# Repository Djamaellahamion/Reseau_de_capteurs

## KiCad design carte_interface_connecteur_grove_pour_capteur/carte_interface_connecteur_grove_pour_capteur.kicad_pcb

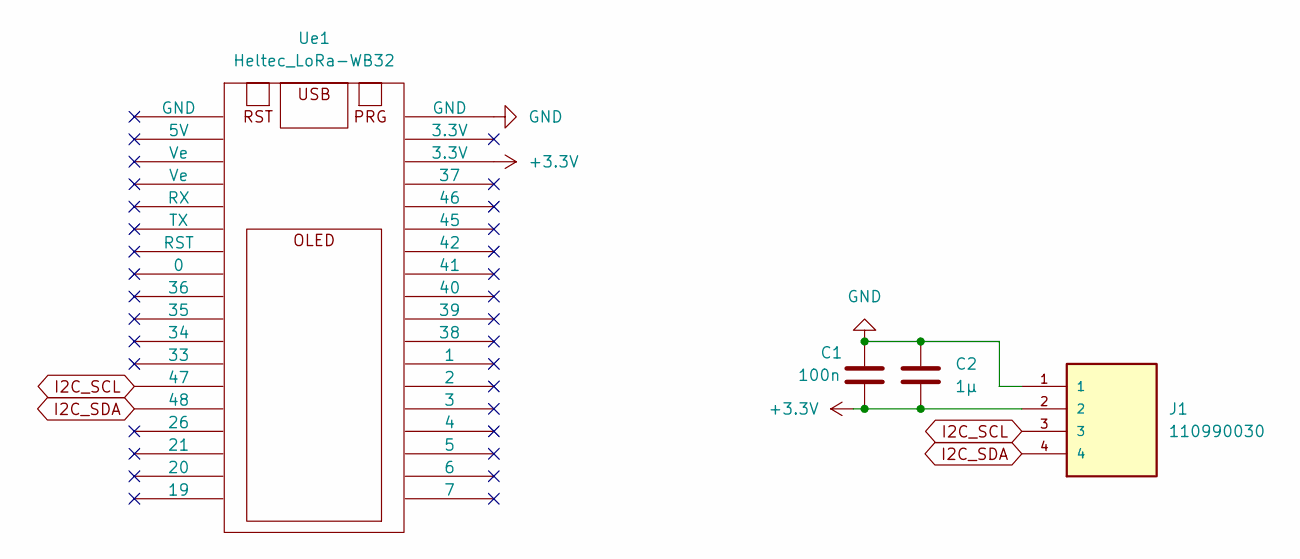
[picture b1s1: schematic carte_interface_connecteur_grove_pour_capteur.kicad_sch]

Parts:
C1: 100n; C_0805
C2: 1µ; C_0805
J1: 110990030; Grove_female_header; PARTREV A
Ue1: Heltec_LoRa-WB32; Heltec_WiFi_LoRa_V2_pin_size_2mm

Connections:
+3.3V: C1.2, C2.2, J1.2, Ue1.34 (3.3V)
GND: C1.1, C2.1, J1.1, Ue1.36 (GND)
I2C_SCL: J1.3, Ue1.13 (47)
I2C_SDA: J1.4, Ue1.14 (48)

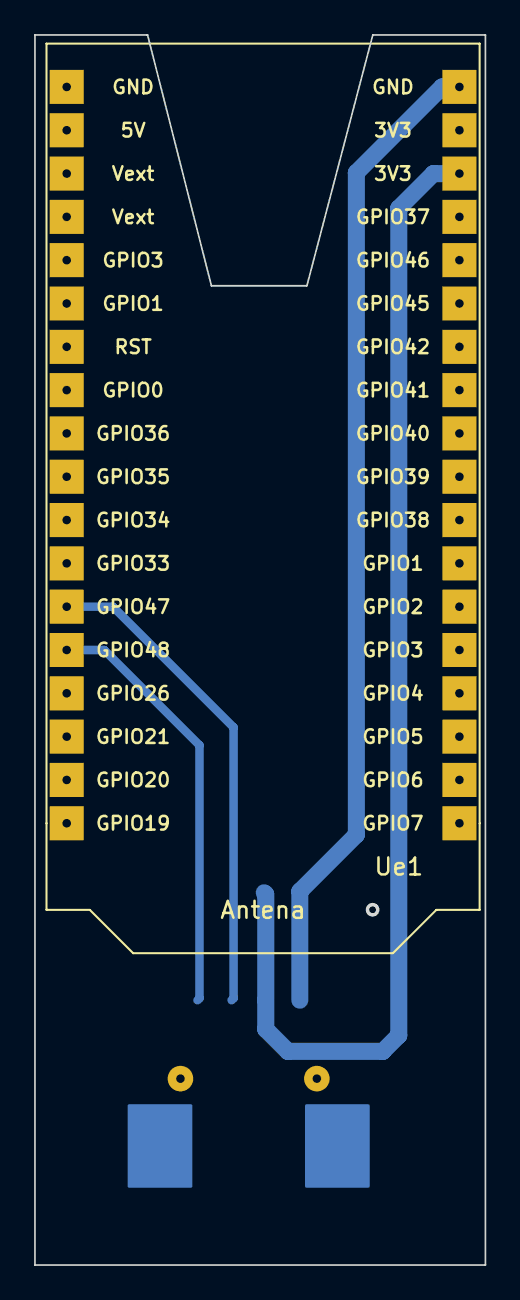
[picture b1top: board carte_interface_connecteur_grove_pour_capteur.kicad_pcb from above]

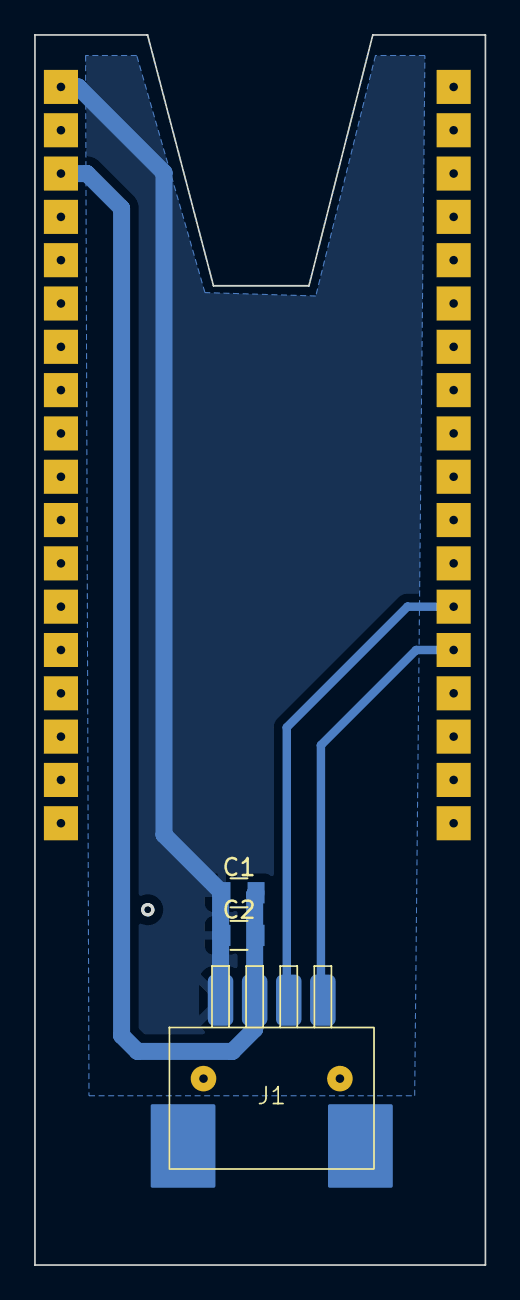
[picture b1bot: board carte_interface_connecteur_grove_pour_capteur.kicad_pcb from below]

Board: 2 copper layers, 26.4 x 72.1 mm, 4 parts (3 on the bottom side), 4 nets.

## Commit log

2023-05-17 Rename LoRaSender_basic.ino to LoRaSender_basic_TTGO.ino
2023-05-17 Rename Wireless Access Raspberry.txt to quelques liens utiles pour Raspberry
2023-05-17 Update quelques liens utiles pour Raspberry
2023-05-23 Create Serveur raspberry Salle blanche
2023-06-03 Update and rename quelques liens utiles pour Raspberry to quelques liens utiles pour Raspberryque
2023-06-03 Update quelques liens utiles pour Raspberryque
2023-06-04 Create IOTstack
2023-06-05 Add files via upload
    Le dossier Radiolib a été modifié et inclus désormais un programme permettant d'utiliser un M5stack Core2 avec un module SPI Sx1262 LoRa waveshare pour créer un Node6. Le programme de la Gateway est 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
